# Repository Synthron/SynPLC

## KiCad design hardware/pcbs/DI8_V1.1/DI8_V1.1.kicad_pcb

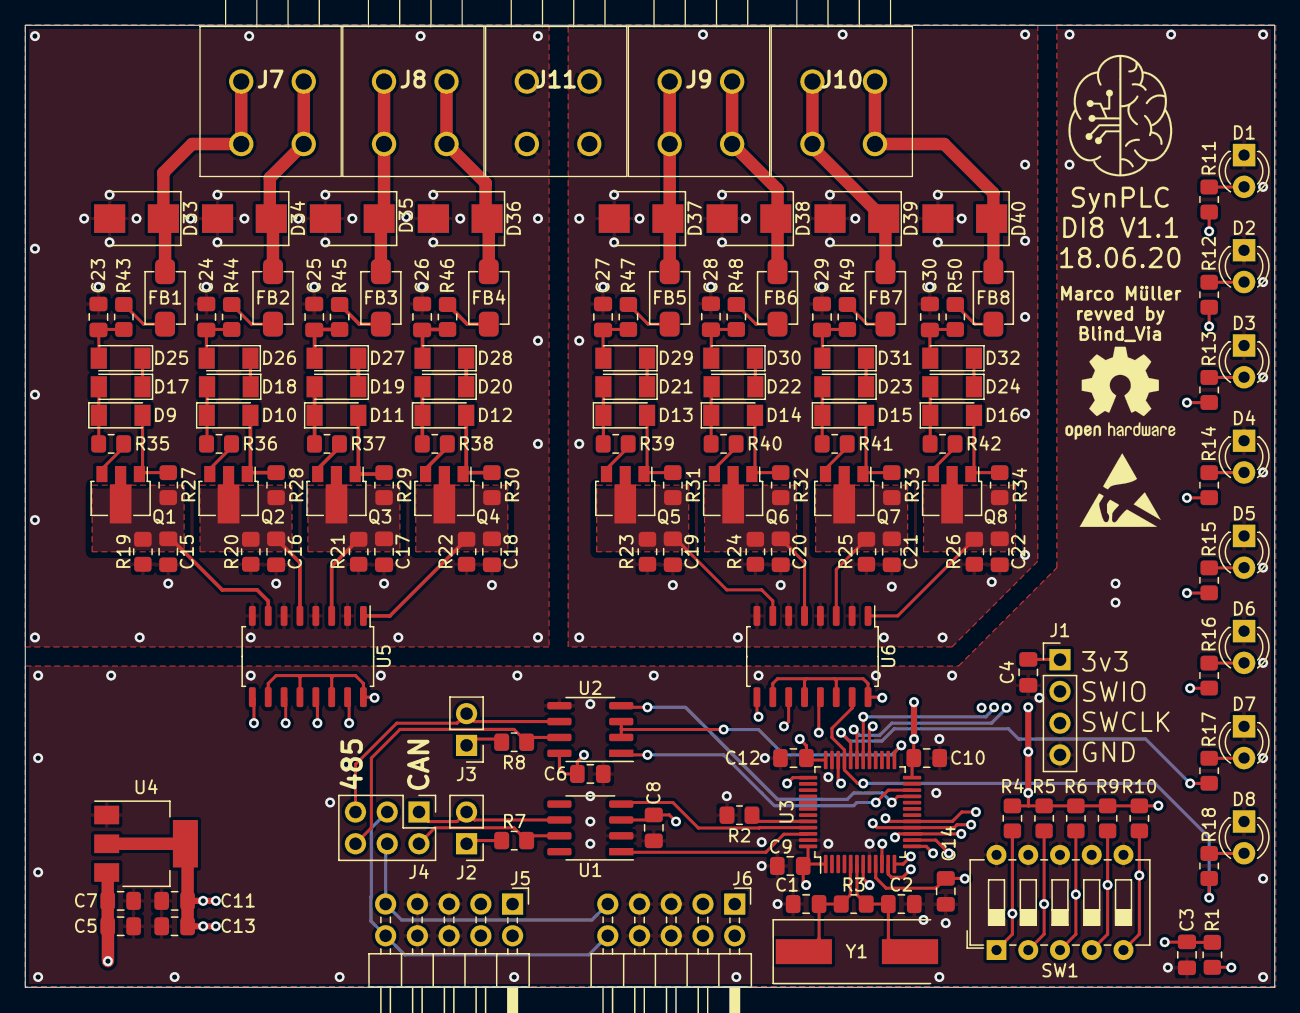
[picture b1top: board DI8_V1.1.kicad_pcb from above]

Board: 4 copper layers, 100.0 x 77.0 mm, 155 parts (0 on the bottom side), 109 nets.

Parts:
C1, C2: 20p; C_0805_2012Metric_Pad1.18x1.45mm_HandSolder
C3, C4, C6, C7, C8, C9, C10, C11, C12, C14: 100n; C_0805_2012Metric_Pad1.18x1.45mm_HandSolder
C5, C13: 1µ; C_0805_2012Metric_Pad1.18x1.45mm_HandSolder
C15, C16, C17, C18, C19, C20, C21, C22: 1n; C_0805_2012Metric_Pad1.18x1.45mm_HandSolder
C23, C24, C25, C26, C27, C28, C29, C30: 470n; C_0805_2012Metric_Pad1.18x1.45mm_HandSolder
D1, D2, D3, D4, D5, D6, D7, D8: LED; LED_D3.0mm
D9, D10, D11, D12, D13, D14, D15, D16: 5v6; D_MiniMELF
D17, D18, D19, D20, D21, D22, D23, D24: 6v8; D_MiniMELF
D25, D26, D27, D28, D29, D30, D31, D32: LL4148; D_MiniMELF
D33, D34, D35, D36, D37, D38, D39, D40: SM6T36A; D_SMB
FB1, FB2, FB3, FB4, FB5, FB6, FB7, FB8: Ferrite_Bead; SMB-001
J1: Conn_01x04; PinHeader_1x04_P2.54mm_Vertical
J2, J3: Conn_01x02; PinHeader_1x02_P2.54mm_Vertical
J4: Conn_02x03_Odd_Even; PinHeader_2x03_P2.54mm_Vertical
J5, J6: Conn_02x05_Odd_Even; PinHeader_2x05_P2.54mm_Horizontal
J7, J8, J9, J10, J11: TBL009-500-02GY-2GY; TBL00950002GY2GY
Q1, Q2, Q3, Q4, Q5, Q6, Q7, Q8: BCX53; SOT-89-3
R1, R2, R4, R5, R6, R9, R10, R43, R44, R45, R46, R47, R48, R49, R50: 1k; R_0805_2012Metric_Pad1.20x1.40mm_HandSolder
R3: 1M; R_0805_2012Metric_Pad1.20x1.40mm_HandSolder
R7: 120; R_0805_2012Metric_Pad1.20x1.40mm_HandSolder
R8: 150; R_0805_2012Metric_Pad1.20x1.40mm_HandSolder
R11, R12, R13, R14, R15, R16, R17, R18: 220; R_0805_2012Metric_Pad1.20x1.40mm_HandSolder
R19, R20, R21, R22, R23, R24, R25, R26: 10k; R_0805_2012Metric_Pad1.20x1.40mm_HandSolder
R27, R28, R29, R30, R31, R32, R33, R34: 47k; R_0805_2012Metric_Pad1.20x1.40mm_HandSolder
R35, R36, R37, R38, R39, R40, R41, R42: 2k2; R_0805_2012Metric_Pad1.20x1.40mm_HandSolder
SW1: SW_DIP_x05; SW_DIP_SPSTx05_Slide_6.7x14.26mm_W7.62mm_P2.54mm_LowProfile
U1: SN65HVD232; SOIC-8_3.9x4.9mm_P1.27mm
U2: MAX485E; SOIC-8_3.9x4.9mm_P1.27mm
U3: STM32F103C8Tx; LQFP-48_7x7mm_P0.5mm
U4: AP1117-33; SOT-223-3_TabPin2
U5, U6: TLP291-4; SOIC-16_4.55x10.3mm_P1.27mm
Y1: 8MHz; Crystal_SMD_HC49-SD

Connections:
+3V3: C4.2, C6.2, C8.2, C9.2, C10.2, C11.2, C12.2, C13.2, C14.2, J1.1, R1.2, R4.2, R5.2, R6.2, R9.2, R10.2, U1.3, U2.8, U3.1, U3.9, U3.24, U3.36, U3.48, U4.2, U5.10, U5.12, U5.14, U5.16, U6.10, U6.12, U6.14, U6.16
BUS+: J4.4, J5.9, J6.9
BUS-: J4.3, J5.10, J6.10
CAN_RD: U1.4, U3.45
CAN_TD: U1.1, U3.46
CH1: R11.2, U3.15, U5.9
CH2: R12.2, U3.16, U5.11
CH3: R13.2, U3.17, U5.13
CH4: R14.2, U3.29, U5.15
CH5: R15.2, U3.30, U6.9
CH6: R16.2, U3.31, U6.11
CH7: R17.2, U3.32, U6.13
CH8: R18.2, U3.33, U6.15
DIR: U2.2, U2.3, U3.25
GND: C1.2, C2.1, C3.1, C4.1, C5.1, C6.1, C7.1, C8.1, C9.1, C10.1, C11.1, C12.1, C13.1, C14.1, D1.1, D2.1, D3.1, D4.1, D5.1, D6.1, D7.1, D8.1, J1.4, J5.5, J5.6, J5.7, J5.8, J6.5, J6.6, J6.7, J6.8, R2.2, SW1.6, SW1.7, SW1.8, SW1.9, SW1.10, U1.2, U2.5, U3.8, U3.23, U3.35, U3.47, U4.1
GND1: C15.1, C16.1, C17.1, C18.1, C23.1, C24.1, C25.1, C26.1, D33.2, D34.2, D35.2, D36.2, J11.1, J11.2, R19.1, R20.1, R21.1, R22.1, U5.2, U5.4, U5.6, U5.8
GND2: C19.1, C20.1, C21.1, C22.1, C27.1, C28.1, C29.1, C30.1, D37.2, D38.2, D39.2, D40.2, J11.3, J11.4, R23.1, R24.1, R25.1, R26.1, U6.2, U6.4, U6.6, U6.8
unnamed: C1.1, R3.2, U3.5, Y1.1
unnamed: C2.2, R3.1, U3.6, Y1.2
unnamed: C3.2, R1.1, U3.7
unnamed: C15.2, Q1.2, R19.2, R27.2, U5.7
unnamed: C16.2, Q2.2, R20.2, R28.2, U5.5
unnamed: C17.2, Q3.2, R21.2, R29.2, U5.3
unnamed: C18.2, Q4.2, R22.2, R30.2, U5.1
unnamed: C19.2, Q5.2, R23.2, R31.2, U6.7
unnamed: C20.2, Q6.2, R24.2, R32.2, U6.5
unnamed: C21.2, Q7.2, R25.2, R33.2, U6.3
unnamed: C22.2, Q8.2, R26.2, R34.2, U6.1
unnamed: C23.2, D25.2, R43.2
unnamed: C24.2, D26.2, R44.2
unnamed: C25.2, D27.2, R45.2
unnamed: C26.2, D28.2, R46.2
unnamed: C27.2, D29.2, R47.2
unnamed: C28.2, D30.2, R48.2
unnamed: C29.2, D31.2, R49.2
unnamed: C30.2, D32.2, R50.2
unnamed: D1.2, R11.1
unnamed: D2.2, R12.1
unnamed: D3.2, R13.1
unnamed: D4.2, R14.1
unnamed: D5.2, R15.1
unnamed: D6.2, R16.1
unnamed: D7.2, R17.1
unnamed: D8.2, R18.1
unnamed: D9.2, Q1.1, R27.1
unnamed: D10.1, D18.2, R36.1
unnamed: D10.2, Q2.1, R28.1
unnamed: D11.1, D19.2, R37.1
unnamed: D11.2, Q3.1, R29.1
unnamed: D12.1, D20.2, R38.1
unnamed: D12.2, Q4.1, R30.1
unnamed: D13.1, D21.2, R39.1
unnamed: D13.2, Q5.1, R31.1
unnamed: D14.1, D22.2, R40.1
unnamed: D14.2, Q6.1, R32.1
unnamed: D15.1, D23.2, R41.1
unnamed: D15.2, Q7.1, R33.1
unnamed: D16.1, D24.2, R42.1
unnamed: D16.2, Q8.1, R34.1
unnamed: D17.1, D25.1
unnamed: D9.1, D17.2, R35.1
unnamed: D18.1, D26.1
unnamed: D19.1, D27.1
unnamed: D20.1, D28.1
unnamed: D21.1, D29.1
unnamed: D22.1, D30.1
unnamed: D23.1, D31.1
unnamed: D24.1, D32.1
unnamed: D33.1, FB1.1, J7.1, J7.2
unnamed: D34.1, FB2.1, J7.3, J7.4
unnamed: D35.1, FB3.1, J8.1, J8.2
unnamed: D36.1, FB4.1, J8.3, J8.4
unnamed: D37.1, FB5.1, J9.1, J9.2
unnamed: D38.1, FB6.1, J9.3, J9.4
unnamed: D39.1, FB7.1, J10.1, J10.2
unnamed: D40.1, FB8.1, J10.3, J10.4
unnamed: FB1.2, R43.1
unnamed: FB2.2, R44.1
unnamed: FB3.2, R45.1
unnamed: FB4.2, R46.1
unnamed: FB5.2, R47.1
unnamed: FB6.2, R48.1
unnamed: FB7.2, R49.1
unnamed: FB8.2, R50.1
unnamed: J2.1, R7.2
unnamed: J2.2, J4.1, U1.6
unnamed: J3.1, R8.2
unnamed: J3.2, J4.5, U2.6
unnamed: J4.2, R7.1, U1.7
unnamed: J4.6, R8.1, U2.7
unnamed: Q1.3, R35.2
unnamed: Q2.3, R36.2
unnamed: Q3.3, R37.2
unnamed: Q4.3, R38.2
unnamed: Q5.3, R39.2
unnamed: Q6.3, R40.2
unnamed: Q7.3, R41.2
unnamed: Q8.3, R42.2
unnamed: R2.1, U3.44
unnamed: R4.1, SW1.1, U3.10
unnamed: R5.1, SW1.2, U3.11
unnamed: R6.1, SW1.3, U3.12
unnamed: R9.1, SW1.4, U3.13
unnamed: R10.1, SW1.5, U3.14
RXD: U2.1, U3.22
SWCLK: J1.3, U3.37
SWIO: J1.2, U3.34
TXD: U2.4, U3.21
VCC: C5.2, C7.2, J5.1, J5.2, J5.3, J5.4, J6.1, J6.2, J6.3, J6.4, U4.3
